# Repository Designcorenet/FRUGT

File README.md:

# FRUGT
An open source, affordable and accessible plant cultivation system.               
Note: This repository is still in its beginning.

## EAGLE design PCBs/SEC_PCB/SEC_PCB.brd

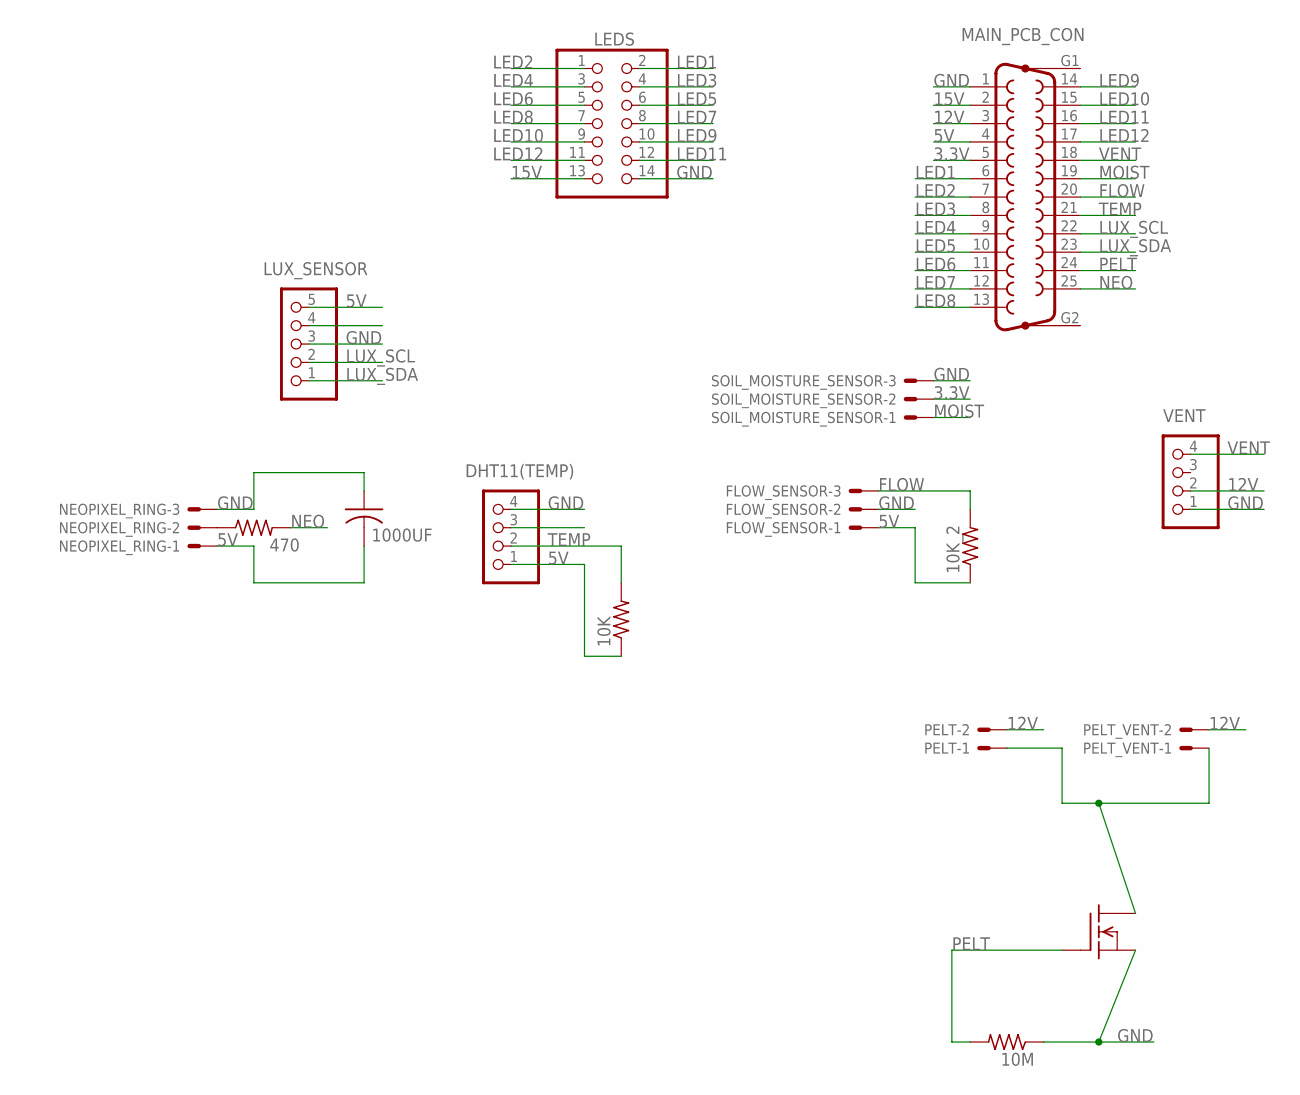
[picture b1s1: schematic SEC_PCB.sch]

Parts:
10K, 10K_2, 10M, 470: FLIPFLOP-RES; 0805-THM
1000UF: C-US050-035X075; C050-035X075
DHT11(TEMP): PINHD-1X4; 1X04
FLOW_SENSOR: JST-XH-03-PIN-LONG-PAD; JST-XH-03-PACKAGE-LONG-PAD
LEDS: PINHD-2X7; 2X07
LUX_SENSOR: PINHD-1X5; 1X05
MAIN_PCB_CON: F25VP
NEOPIXEL_RING: JST-XH-03-PIN-LONG-PAD; JST-XH-03-PACKAGE-LONG-PAD
PELT: JST-XH-02-PIN-LONG-PAD; JST-XH-02-PACKAGE-LONG-PAD
PELT_TRANSISTOR: FQN1N50C; TO92
PELT_VENT: JST-XH-02-PIN-LONG-PAD; JST-XH-02-PACKAGE-LONG-PAD
SOIL_MOISTURE_SENSOR: JST-XH-03-PIN-LONG-PAD; JST-XH-03-PACKAGE-LONG-PAD
VENT: PINHD-1X4; 1X04

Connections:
3.3V: MAIN_PCB_CON.5, SOIL_MOISTURE_SENSOR.2
5V: 10K.1, 10K_2.1, 1000UF.2, DHT11(TEMP).1, FLOW_SENSOR.1, LUX_SENSOR.5, MAIN_PCB_CON.4, NEOPIXEL_RING.1
12V: MAIN_PCB_CON.3, PELT.2, PELT_VENT.2, VENT.2
15V: LEDS.13, MAIN_PCB_CON.2
FLOW: 10K_2.2, FLOW_SENSOR.3, MAIN_PCB_CON.20
GND: 10M.1, 1000UF.1, DHT11(TEMP).4, FLOW_SENSOR.2, LEDS.14, LUX_SENSOR.3, MAIN_PCB_CON.1, NEOPIXEL_RING.3, PELT_TRANSISTOR.3 (S), SOIL_MOISTURE_SENSOR.3, VENT.1
LED1: LEDS.2, MAIN_PCB_CON.6
LED2: LEDS.1, MAIN_PCB_CON.7
LED3: LEDS.4, MAIN_PCB_CON.8
LED4: LEDS.3, MAIN_PCB_CON.9
LED5: LEDS.6, MAIN_PCB_CON.10
LED6: LEDS.5, MAIN_PCB_CON.11
LED7: LEDS.8, MAIN_PCB_CON.12
LED8: LEDS.7, MAIN_PCB_CON.13
LED9: LEDS.10, MAIN_PCB_CON.14
LED10: LEDS.9, MAIN_PCB_CON.15
LED11: LEDS.12, MAIN_PCB_CON.16
LED12: LEDS.11, MAIN_PCB_CON.17
LUX_SCL: LUX_SENSOR.2, MAIN_PCB_CON.22
LUX_SDA: LUX_SENSOR.1, MAIN_PCB_CON.23
MOIST: MAIN_PCB_CON.19, SOIL_MOISTURE_SENSOR.1
unnamed: 470.1, NEOPIXEL_RING.2
unnamed: PELT.1, PELT_TRANSISTOR.2 (D), PELT_VENT.1
NEO: 470.2, MAIN_PCB_CON.25
PELT: 10M.2, MAIN_PCB_CON.24, PELT_TRANSISTOR.1 (G)
TEMP: 10K.2, DHT11(TEMP).2, MAIN_PCB_CON.21
VENT: MAIN_PCB_CON.18, VENT.4

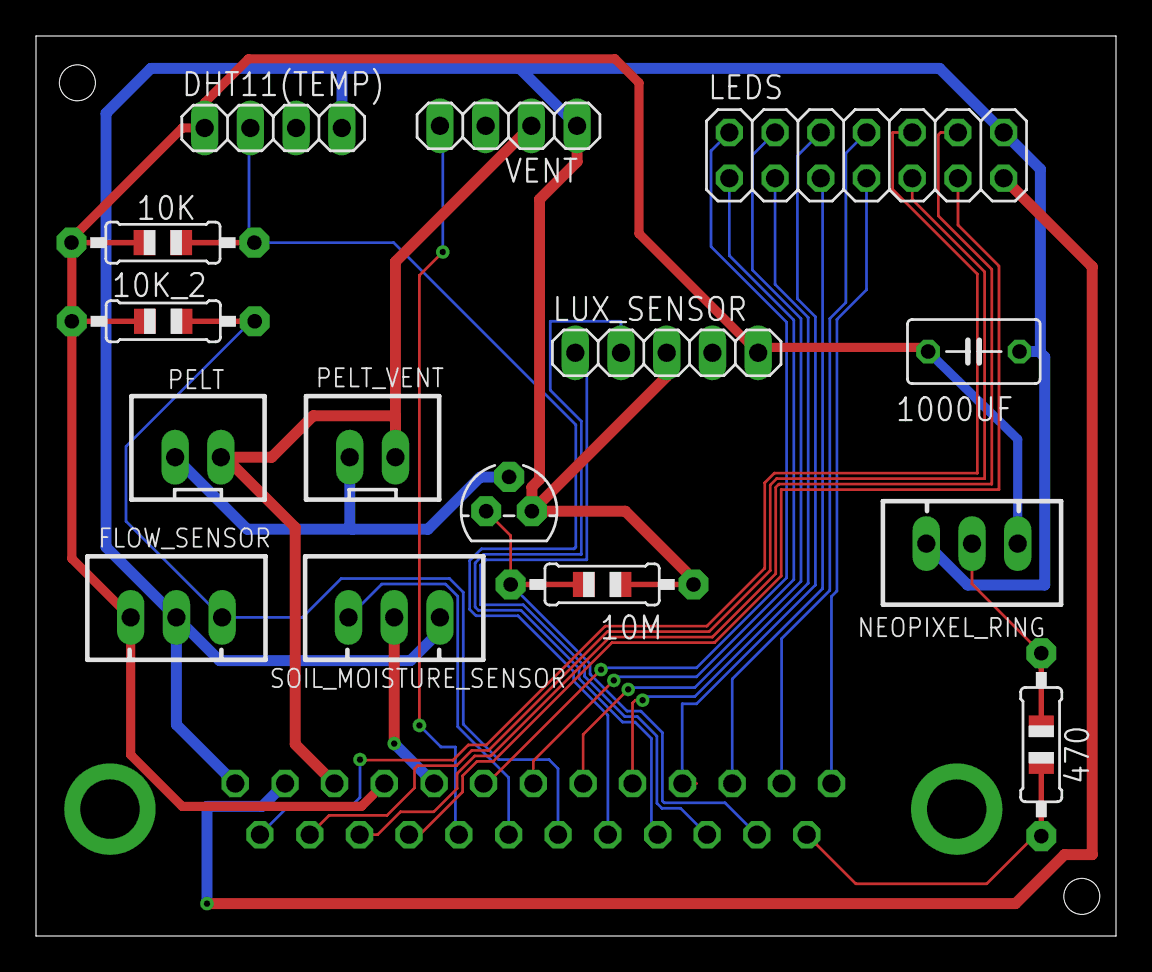
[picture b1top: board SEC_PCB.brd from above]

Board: 2 copper layers, 60.0 x 50.0 mm, 16 parts (1 on the bottom side), 27 nets.

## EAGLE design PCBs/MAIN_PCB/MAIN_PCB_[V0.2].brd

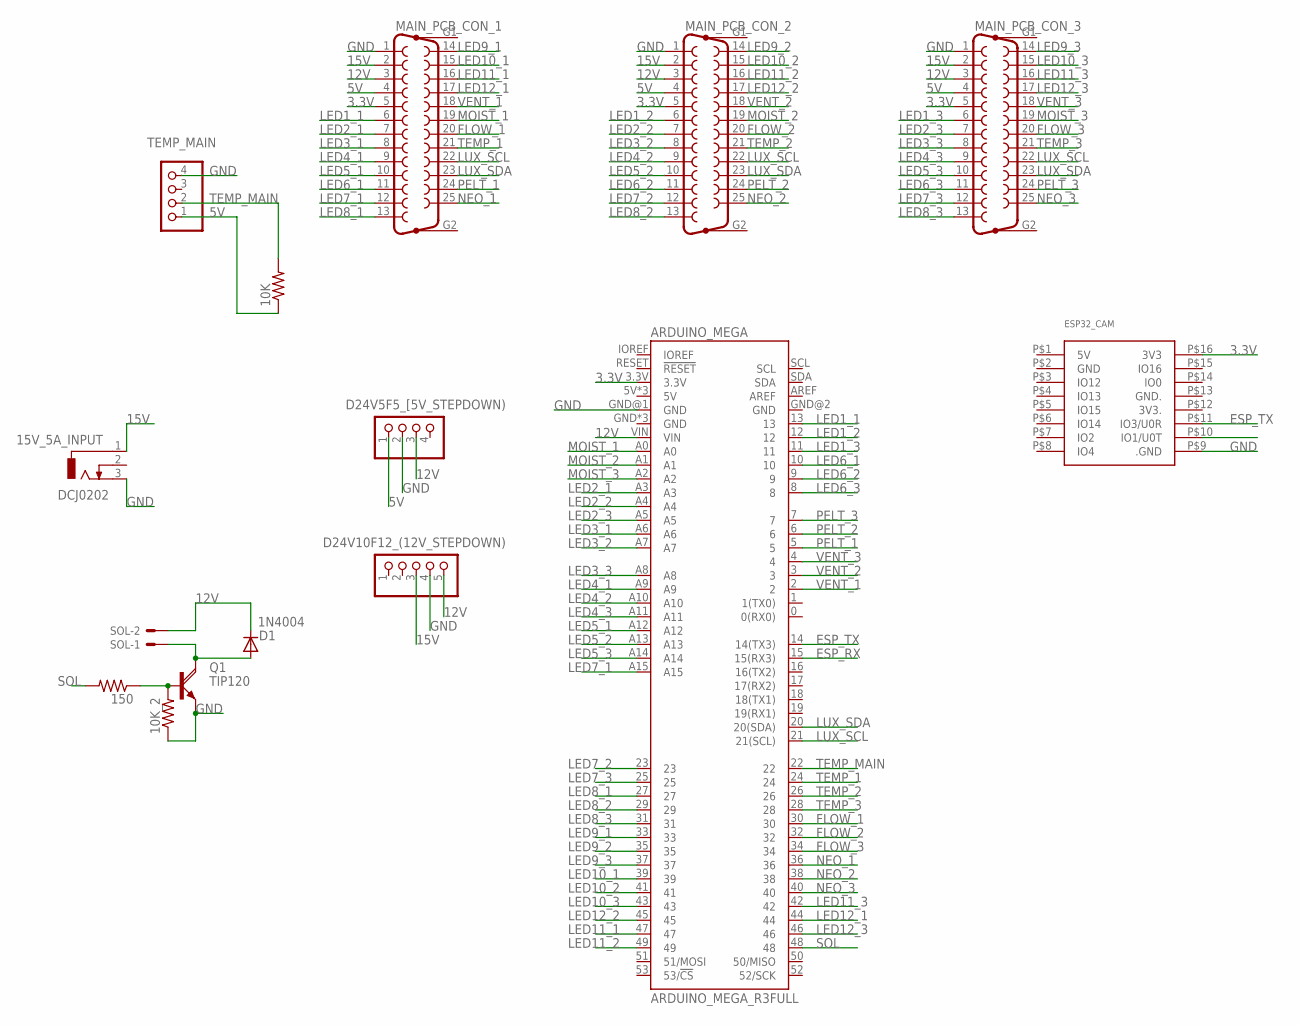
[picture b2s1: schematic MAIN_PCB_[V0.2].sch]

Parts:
10K, 10K_2, 150: FLIPFLOP-RES; 0805-THM
15V_5A_INPUT: DCJ0202
ARDUINO_MEGA: ARDUINO_MEGA_R3FULL; ARDUINO_MEGA_NO_SILK
D1: 1N4004; DO41-10
D24V5F5_[5V_STEPDOWN): PINHD-1X4; 1X04
D24V10F12_(12V_STEPDOWN): PINHD-1X5; 1X05
ESP32_CAM: ESP32-CAM
MAIN_PCB_CON_1, MAIN_PCB_CON_2, MAIN_PCB_CON_3: F25VP
Q1: TIP120; TO220AH
SOL: JST-XH-02-PIN-LONG-PAD; JST-XH-02-PACKAGE-LONG-PAD
TEMP_MAIN: PINHD-1X4; 1X04

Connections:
3.3V: ARDUINO_MEGA.3.3V, ESP32_CAM.P$16 (3V3), MAIN_PCB_CON_1.5, MAIN_PCB_CON_2.5, MAIN_PCB_CON_3.5
5V: 10K.1, D24V5F5_[5V_STEPDOWN).1, MAIN_PCB_CON_1.4, MAIN_PCB_CON_2.4, MAIN_PCB_CON_3.4, TEMP_MAIN.1
12V: ARDUINO_MEGA.VIN, D1.C, D24V5F5_[5V_STEPDOWN).3, D24V10F12_(12V_STEPDOWN).5, MAIN_PCB_CON_1.3, MAIN_PCB_CON_2.3, MAIN_PCB_CON_3.3, SOL.2
15V: 15V_5A_INPUT.1, D24V10F12_(12V_STEPDOWN).3, MAIN_PCB_CON_1.2, MAIN_PCB_CON_2.2, MAIN_PCB_CON_3.2
ESP_RX: ARDUINO_MEGA.15 (15(RX3)), ESP32_CAM.P$10 (IO1/U0T)
ESP_TX: ARDUINO_MEGA.14 (14(TX3)), ESP32_CAM.P$11 (IO3/U0R)
FLOW_1: ARDUINO_MEGA.30, MAIN_PCB_CON_1.20
FLOW_2: ARDUINO_MEGA.32, MAIN_PCB_CON_2.20
FLOW_3: ARDUINO_MEGA.34, MAIN_PCB_CON_3.20
GND: 10K_2.1, 15V_5A_INPUT.3, ARDUINO_MEGA.GND@1 (GND), D24V5F5_[5V_STEPDOWN).2, D24V10F12_(12V_STEPDOWN).4, ESP32_CAM.P$9 (.GND), MAIN_PCB_CON_1.1, MAIN_PCB_CON_2.1, MAIN_PCB_CON_3.1, Q1.E, TEMP_MAIN.4
LED1_1: ARDUINO_MEGA.13, MAIN_PCB_CON_1.6
LED1_2: ARDUINO_MEGA.12, MAIN_PCB_CON_2.6
LED1_3: ARDUINO_MEGA.11, MAIN_PCB_CON_3.6
LED2_1: ARDUINO_MEGA.A3, MAIN_PCB_CON_1.7
LED2_2: ARDUINO_MEGA.A4, MAIN_PCB_CON_2.7
LED2_3: ARDUINO_MEGA.A5, MAIN_PCB_CON_3.7
LED3_1: ARDUINO_MEGA.A6, MAIN_PCB_CON_1.8
LED3_2: ARDUINO_MEGA.A7, MAIN_PCB_CON_2.8
LED3_3: ARDUINO_MEGA.A8, MAIN_PCB_CON_3.8
LED4_1: ARDUINO_MEGA.A9, MAIN_PCB_CON_1.9
LED4_2: ARDUINO_MEGA.A10, MAIN_PCB_CON_2.9
LED4_3: ARDUINO_MEGA.A11, MAIN_PCB_CON_3.9
LED5_1: ARDUINO_MEGA.A12, MAIN_PCB_CON_1.10
LED5_2: ARDUINO_MEGA.A13, MAIN_PCB_CON_2.10
LED5_3: ARDUINO_MEGA.A14, MAIN_PCB_CON_3.10
LED6_1: ARDUINO_MEGA.10, MAIN_PCB_CON_1.11
LED6_2: ARDUINO_MEGA.9, MAIN_PCB_CON_2.11
LED6_3: ARDUINO_MEGA.8, MAIN_PCB_CON_3.11
LED7_1: ARDUINO_MEGA.A15, MAIN_PCB_CON_1.12
LED7_2: ARDUINO_MEGA.23, MAIN_PCB_CON_2.12
LED7_3: ARDUINO_MEGA.25, MAIN_PCB_CON_3.12
LED8_1: ARDUINO_MEGA.27, MAIN_PCB_CON_1.13
LED8_2: ARDUINO_MEGA.29, MAIN_PCB_CON_2.13
LED8_3: ARDUINO_MEGA.31, MAIN_PCB_CON_3.13
LED9_1: ARDUINO_MEGA.33, MAIN_PCB_CON_1.14
LED9_2: ARDUINO_MEGA.35, MAIN_PCB_CON_2.14
LED9_3: ARDUINO_MEGA.37, MAIN_PCB_CON_3.14
LED10_1: ARDUINO_MEGA.39, MAIN_PCB_CON_1.15
LED10_2: ARDUINO_MEGA.41, MAIN_PCB_CON_2.15
LED10_3: ARDUINO_MEGA.43, MAIN_PCB_CON_3.15
LED11_1: ARDUINO_MEGA.47, MAIN_PCB_CON_1.16
LED11_2: ARDUINO_MEGA.49, MAIN_PCB_CON_2.16
LED11_3: ARDUINO_MEGA.42, MAIN_PCB_CON_3.16
LED12_1: ARDUINO_MEGA.44, MAIN_PCB_CON_1.17
LED12_2: ARDUINO_MEGA.45, MAIN_PCB_CON_2.17
LED12_3: ARDUINO_MEGA.46, MAIN_PCB_CON_3.17
LUX_SCL: ARDUINO_MEGA.21 (21(SCL)), MAIN_PCB_CON_1.22, MAIN_PCB_CON_2.22, MAIN_PCB_CON_3.22
LUX_SDA: ARDUINO_MEGA.20 (20(SDA)), MAIN_PCB_CON_1.23, MAIN_PCB_CON_2.23, MAIN_PCB_CON_3.23
MOIST_1: ARDUINO_MEGA.A0, MAIN_PCB_CON_1.19
MOIST_2: ARDUINO_MEGA.A1, MAIN_PCB_CON_2.19
MOIST_3: ARDUINO_MEGA.A2, MAIN_PCB_CON_3.19
unnamed: D1.A, Q1.C, SOL.1
unnamed: 10K_2.2, 150.1, Q1.B
NEO_1: ARDUINO_MEGA.36, MAIN_PCB_CON_1.25
NEO_2: ARDUINO_MEGA.38, MAIN_PCB_CON_2.25
NEO_3: ARDUINO_MEGA.40, MAIN_PCB_CON_3.25
PELT_1: ARDUINO_MEGA.5, MAIN_PCB_CON_1.24
PELT_2: ARDUINO_MEGA.6, MAIN_PCB_CON_2.24
PELT_3: ARDUINO_MEGA.7, MAIN_PCB_CON_3.24
SOL: 150.2, ARDUINO_MEGA.48
TEMP_1: ARDUINO_MEGA.24, MAIN_PCB_CON_1.21
TEMP_2: ARDUINO_MEGA.26, MAIN_PCB_CON_2.21
TEMP_3: ARDUINO_MEGA.28, MAIN_PCB_CON_3.21
TEMP_MAIN: 10K.2, ARDUINO_MEGA.22, TEMP_MAIN.2
VENT_1: ARDUINO_MEGA.2, MAIN_PCB_CON_1.18
VENT_2: ARDUINO_MEGA.3, MAIN_PCB_CON_2.18
VENT_3: ARDUINO_MEGA.4, MAIN_PCB_CON_3.18

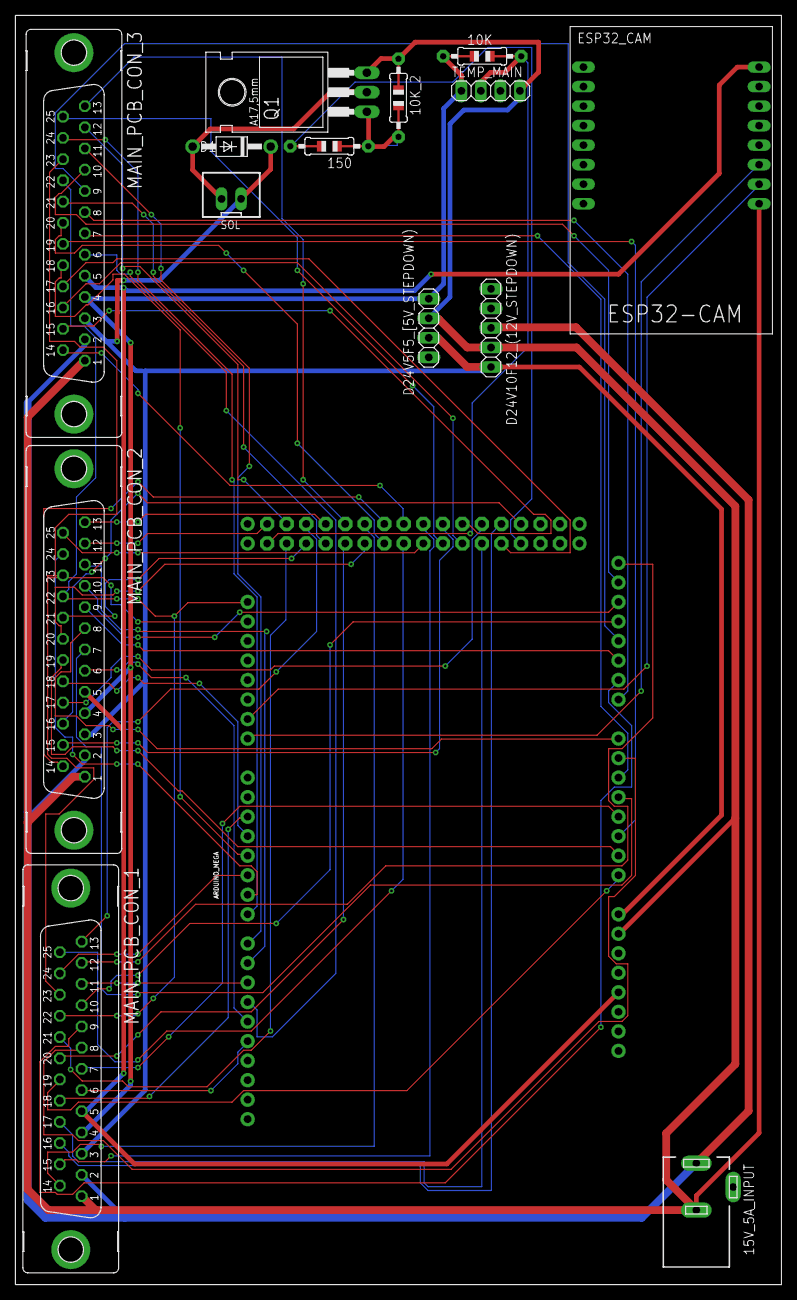
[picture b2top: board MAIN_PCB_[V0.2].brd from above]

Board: 2 copper layers, 99.7 x 165.2 mm, 15 parts (0 on the bottom side), 67 nets.

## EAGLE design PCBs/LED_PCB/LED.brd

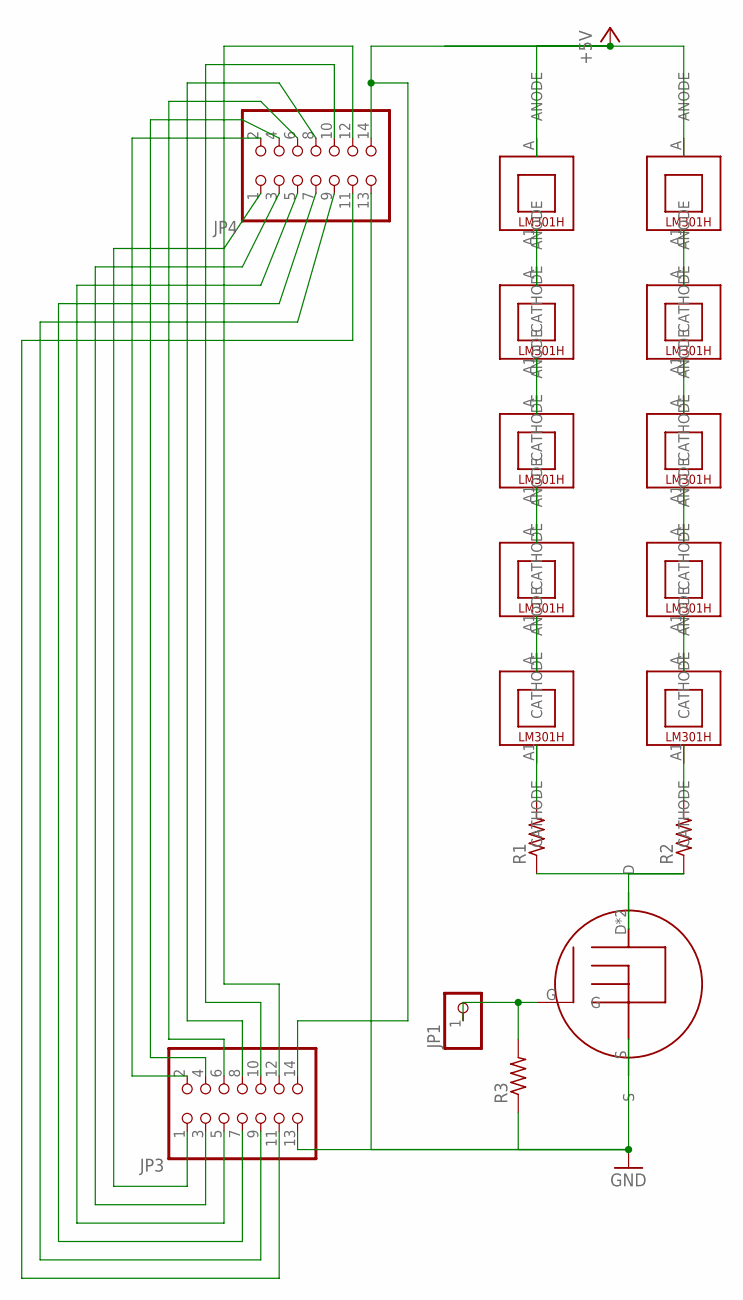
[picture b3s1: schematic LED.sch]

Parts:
JP1: PINHD-1X1; 1X01
JP3, JP4: PINHD-2X7; 2X07
R1, R2, R3: FLIPFLOP-RES; 0805-THM
U$1, U$2, U$3, U$4, U$5, U$6, U$7, U$8, U$9, U$10: LM301H; SPMWHD32AMH5XAT5SL
U$11: SOT223; S

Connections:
GND: JP3.13, JP4.13, R3.1, U$11.S
unnamed: JP3.12, JP4.12
unnamed: JP3.1, JP4.1
unnamed: R2.2, U$10.A1 (CATHODE)
unnamed: U$9.A1 (CATHODE), U$10.A (ANODE)
unnamed: U$8.A1 (CATHODE), U$9.A (ANODE)
unnamed: U$7.A1 (CATHODE), U$8.A (ANODE)
unnamed: U$6.A1 (CATHODE), U$7.A (ANODE)
unnamed: R1.2, U$5.A1 (CATHODE)
unnamed: U$4.A1 (CATHODE), U$5.A (ANODE)
unnamed: U$3.A1 (CATHODE), U$4.A (ANODE)
unnamed: U$2.A1 (CATHODE), U$3.A (ANODE)
unnamed: U$1.A1 (CATHODE), U$2.A (ANODE)
unnamed: JP3.2, JP4.2
unnamed: JP3.3, JP4.3
unnamed: JP3.4, JP4.4
unnamed: JP3.5, JP4.5
unnamed: JP3.6, JP4.6
unnamed: JP3.7, JP4.7
unnamed: JP3.8, JP4.8
unnamed: JP3.9, JP4.9
unnamed: JP3.10, JP4.10
unnamed: JP3.11, JP4.11
unnamed: JP1.1, R3.2, U$11.G
VCC: JP3.14, JP4.14, U$1.A (ANODE), U$6.A (ANODE)
_GND: R1.1, R2.1, U$11.D, U$11.DKLEIN (D)

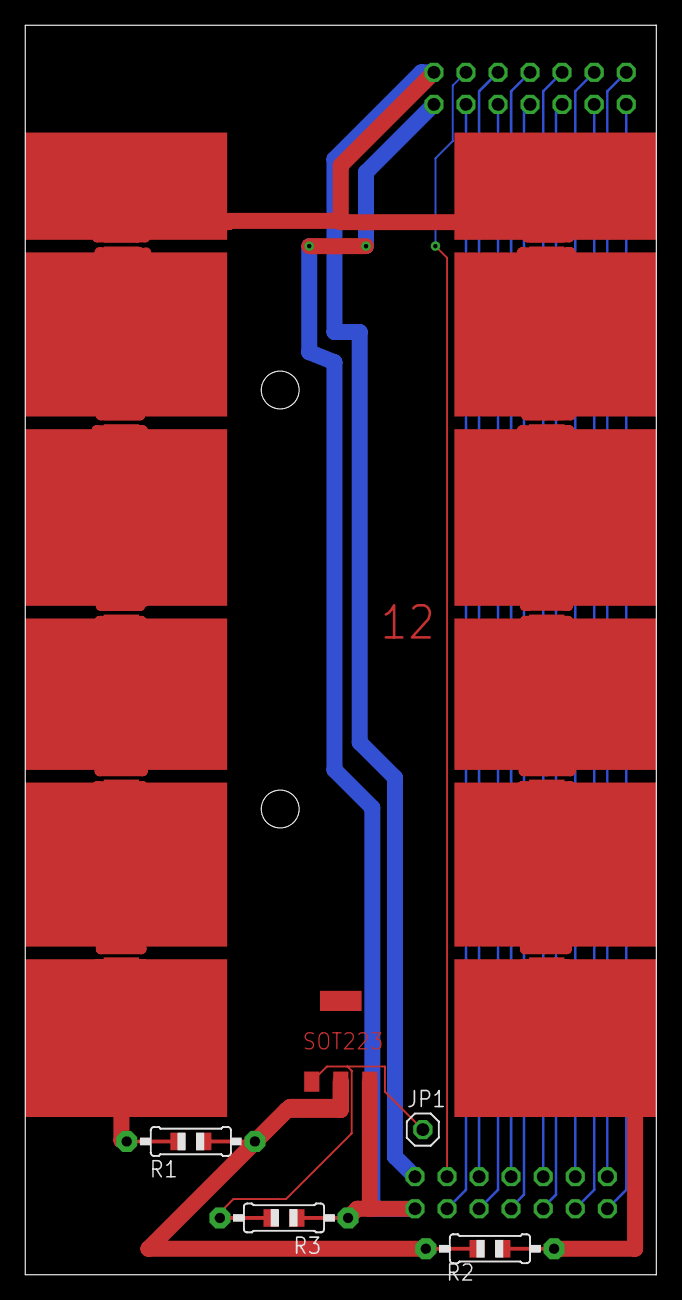
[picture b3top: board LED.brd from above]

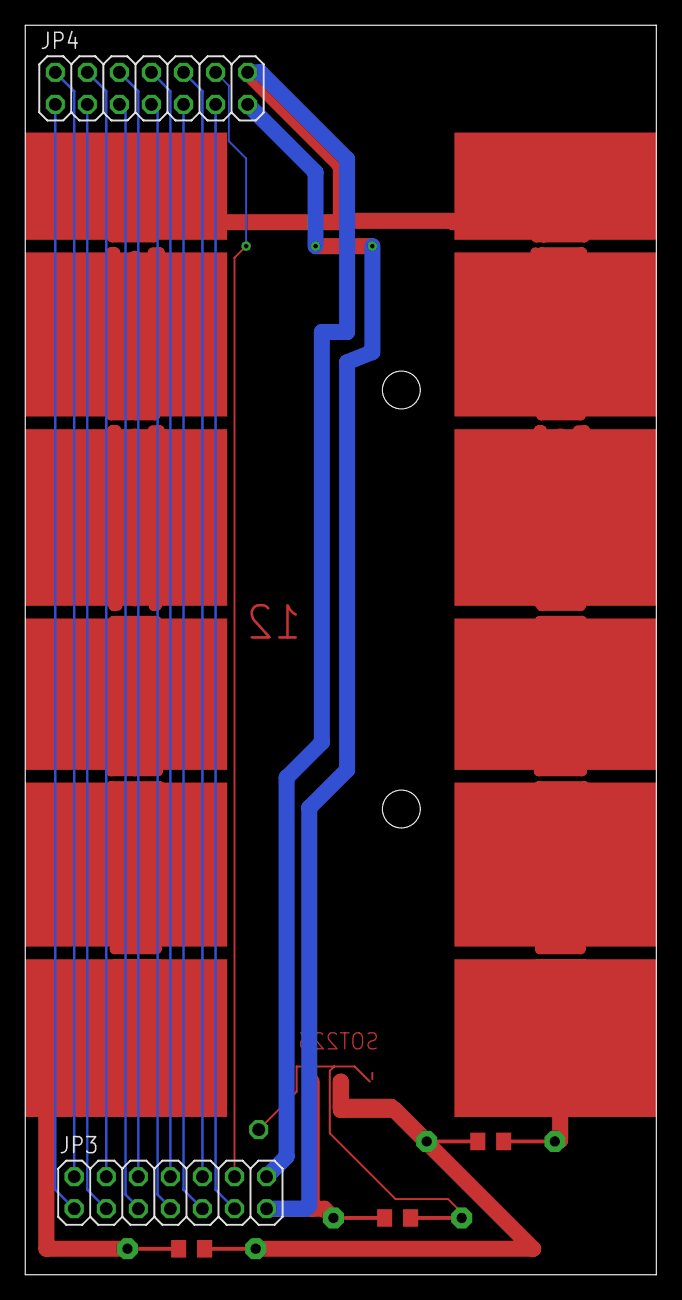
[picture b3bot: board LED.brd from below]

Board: 2 copper layers, 50.0 x 99.0 mm, 17 parts (2 on the bottom side), 26 nets.

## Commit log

2022-09-04 Create Drawings
2022-10-21 main code Arduino MEGA
2022-10-21 Platformio fix i guess.....
2022-10-21 ESPCAM main

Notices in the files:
parts and their libraries:
SparkFun-Boards: Licensing: Creative Commons ShareAlike 4.0 International - https://creativecommons.org/licenses/by-sa/4.0
